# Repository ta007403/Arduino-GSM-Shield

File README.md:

Smart Coin Machine PCB (v2.1)

This project is a custom PCB for smart coin and bill acceptor machines, designed to simplify wiring, assembly, and integration with GSM modules, Arduino, and Raspberry Pi.

✨ Features

Plug & Play Wiring

Just connect +12V DC input via screw terminals.

Direct connections for coin acceptor, bill acceptor, buzzer, and status LEDs.

GSM Module Support

Compatible with SIM800L and SIM800C.

On-board relay to enable/disable GSM module.

Reset GSM via dedicated relay (Arduino Pin 7).

Built-in DC-DC step-down regulator (LM2596S) provides stable +4V supply for GSM.

Relays & Control

Coin Enable Relay → controlled by Raspberry Pi (Pin 17).

GSM Enable Relay → power cycle or disable GSM when needed.

Power Loss Relay → detect and respond to AC mains failures.

Indicators & Status LEDs

Arduino Pin 8 → Blue LED status output.

Raspberry Pi Pin 27 → Green LED status output.

GSM status LED indicators (Orange).

220VAC Detection

Input and output connectors for 220VAC detection sensor.

Useful for monitoring AC mains availability.

----------------------------------------------------------------------------------------

📐 Hardware Overview

Main components visible on the PCB:

LM2596S DC-DC Buck Converter (12V → 4V for GSM).

3 Relays:

Coin Enable Relay

GSM Enable/Reset Relay

Power Loss Relay

Connectors:

12V DC input

Coin acceptor

Bill acceptor

Buzzer

LEDs (Arduino, Raspberry Pi, GSM)

220VAC detection input/output

GSM Module Slot (SIM800L/SIM800C footprint).

(See PCB layout in uno-r4-shield-template__Assembly.pdf
 for detailed pinouts)
.

----------------------------------------------------------------------------------------

🔌 Pin Mapping
Function	Controller	Pin
Coin Enable	Raspberry Pi	GPIO17
LED Status (Green)	Raspberry Pi	GPIO27
LED Status (Blue)	Arduino	Pin 8
GSM Reset	Arduino	Pin 7
⚡ Power

Input: +12V DC

Internal Regulator: LM2596S → +4V for GSM

Relays and acceptors powered directly from +12V line.

----------------------------------------------------------------------------------------

🚀 Use Case

This PCB is ideal for:

Smart vending or refill machines.

Coin/bill based Bitcoin Lightning machines.

GSM-enabled kiosks requiring reliable reset and status handling.

----------------------------------------------------------------------------------------

📂 Repository Contents

Smart Coin PCB Version 2.1.JPG → Rendered 3D PCB view.

uno-r4-shield-template__Assembly.pdf → PCB layout & assembly reference.

README.md → This documentation.

----------------------------------------------------------------------------------------

🛠️ Assembly Notes

Connect +12V DC power input.

Wire coin and bill acceptors into screw terminals.

Install GSM module (SIM800L or SIM800C).

Connect buzzer and LED indicators.

Connect Raspberry Pi/Arduino control lines as per pin mapping.

----------------------------------------------------------------------------------------

📜 License

This project is free to use as hobby project or commercial

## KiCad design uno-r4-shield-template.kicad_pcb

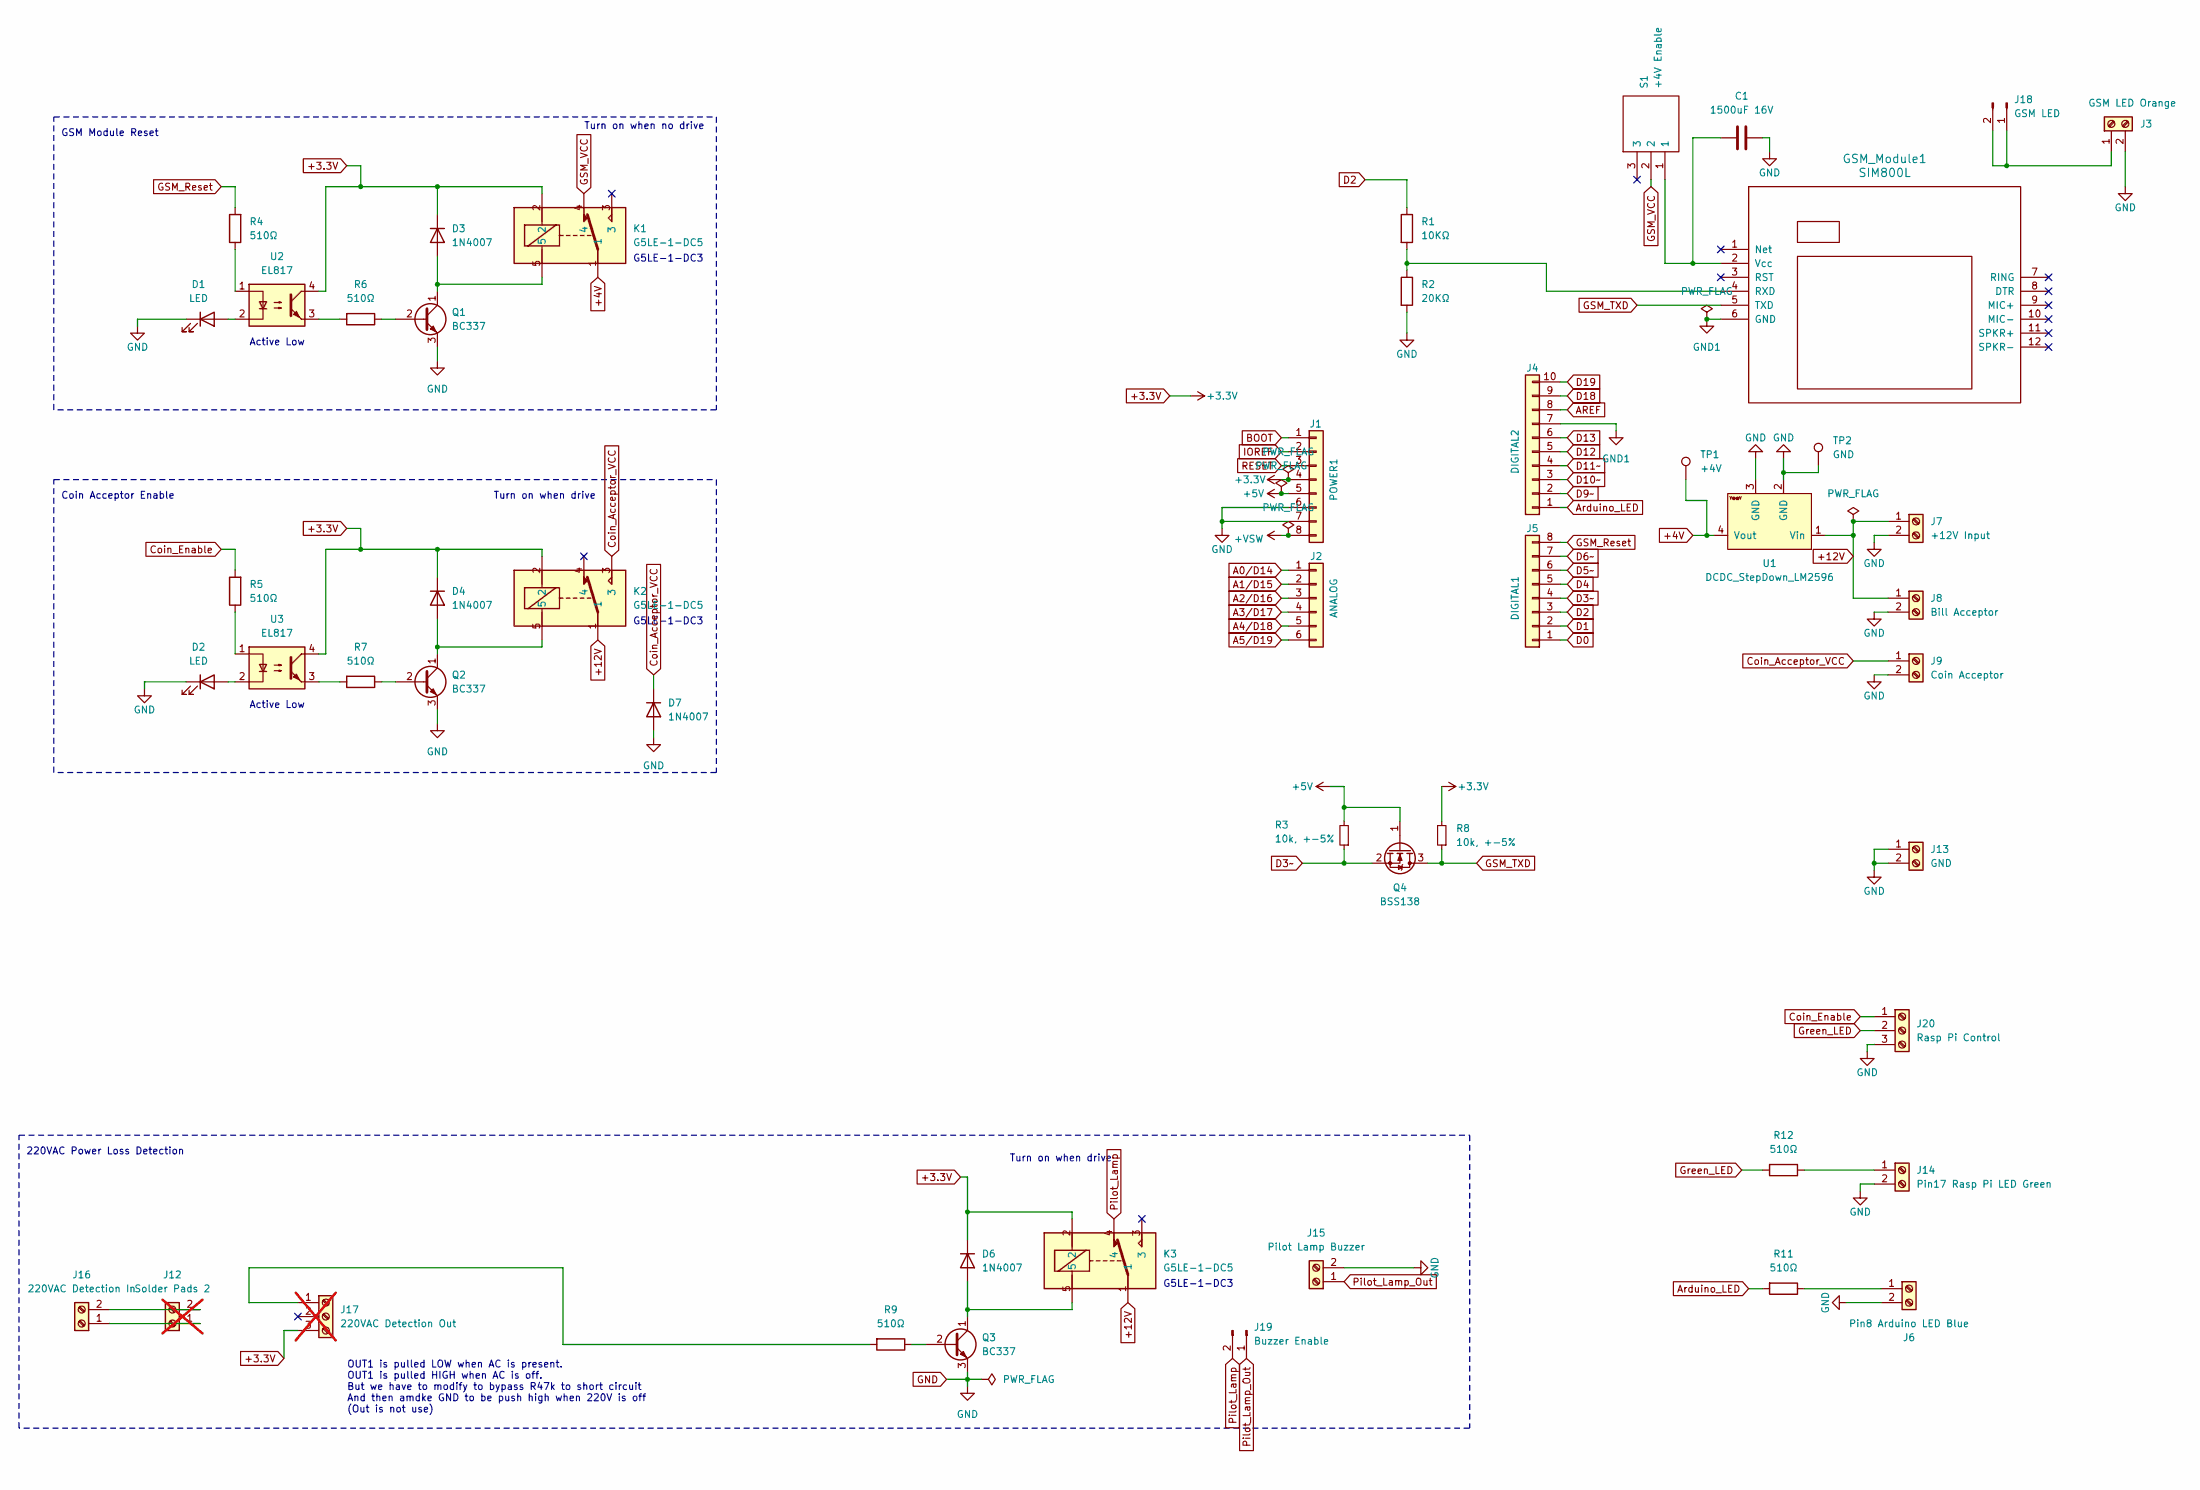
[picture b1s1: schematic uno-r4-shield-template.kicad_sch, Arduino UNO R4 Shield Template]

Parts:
C1: 1500uF 16V; CP_Radial_D10.0mm_P5.00mm
D1, D2: LED; LED_D3.0mm
D3, D4, D6, D7: 1N4007; D_DO-41_SOD81_P10.16mm_Horizontal
GSM_Module1: SIM800L
J1: POWER1; PinHeader_1x08_P2.54mm_Vertical
J2: ANALOG; PinHeader_1x06_P2.54mm_Vertical
J3: GSM LED Orange; TerminalBlock_Phoenix_MKDS-1,5-2-5.08_1x02_P5.08mm_Horizont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
J4: DIGITAL2; PinHeader_1x10_P2.54mm_Vertical
J5: DIGITAL1; PinHeader_1x08_P2.54mm_Vertical
J6: Pin8 Arduino LED Blue; TerminalBlock_Phoenix_MKDS-1,5-2-5.08_1x02_P5.08mm_Horizont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
J7: +12V Input; TerminalBlock_Phoenix_MKDS-1,5-2-5.08_1x02_P5.08mm_Horizont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
J8: Bill Acceptor; TerminalBlock_Phoenix_MKDS-1,5-2-5.08_1x02_P5.08mm_Horizont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
J9: Coin Acceptor; TerminalBlock_Phoenix_MKDS-1,5-2-5.08_1x02_P5.08mm_Horizont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
J12: Solder Pads 2; TerminalBlock_Phoenix_MKDS-1,5-2-5.08_1x02_P5.08mm_Horizont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; not fitted
J13: GND; TerminalBlock_Phoenix_MKDS-1,5-2-5.08_1x02_P5.08mm_Horizont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
J14: Pin17 Rasp Pi LED Green; TerminalBlock_Phoenix_MKDS-1,5-2-5.08_1x02_P5.08mm_Horizont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
J15: Pilot Lamp Buzzer; TerminalBlock_Phoenix_MKDS-1,5-2-5.08_1x02_P5.08mm_Horizont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
J16: 220VAC Detection In; TerminalBlock_Phoenix_MKDS-1,5-2-5.08_1x02_P5.08mm_Horizont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
J17: 220VAC Detection Out; TerminalBlock_Phoenix_MKDS-1,5-3-5.08_1x03_P5.08mm_Horizont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; not fitted
J18: GSM LED; PinHeader_1x02_P2.54mm_Vertical
J19: Buzzer Enable; PinHeader_1x02_P2.54mm_Vertical
J20: Rasp Pi Control; TerminalBlock_Phoenix_MKDS-1,5-3-5.08_1x03_P5.08mm_Horizont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
K1, K2, K3: G5LE-1-DC5; G5LE-1; Mouser Part Number 653-G5LE-1-DC5
Q1, Q2, Q3: BC337; TO-92_Inline
Q4: BSS138; SOT-23; Mfr. Part # BSS138
R1: 10KΩ; R_Axial_DIN0207_L6.3mm_D2.5mm_P10.16mm_Horizontal
R2: 20KΩ; R_Axial_DIN0207_L6.3mm_D2.5mm_P10.16mm_Horizontal
R3, R8: 10k, +-5%; R_Axial_DIN0204_L3.6mm_D1.6mm_P5.08mm_Horizontal; Mfr. Part # RT0402FRE0710KL; LCSC Part # C25804
R4, R5, R6, R7, R9, R11, R12: 510Ω; R_Axial_DIN0207_L6.3mm_D2.5mm_P10.16mm_Horizontal
S1: +4V Enable; 2MS1T1B3M2QES; Mouser Part Number 118-2MS1T1B3M2QES
TP1: +4V; TestPoint_Pad_1.0x1.0mm
TP2: GND; TestPoint_Pad_1.0x1.0mm
U1: DCDC_StepDown_LM2596; YAAJ_DCDC_StepDown_LM2596
U2, U3: EL817; DIP-4_W7.62mm

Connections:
+3.3V: D3.1 (K), D4.1 (K), D6.1 (K), J1.4, J17.3, K1.2, K2.2, K3.2, R8.2, U2.4, U3.4
+4V: K1.1, TP1.1, U1.4 (Vout)
+5V: J1.5, Q4.1 (G), R3.2
+12V: J7.1, J8.1, K2.1, K3.1, U1.1 (Vin)
+VSW: J1.8
A0/D14: J2.1
A1/D15: J2.2
A2/D16: J2.3
A3/D17: J2.4
A4/D18: J2.5
A5/D19: J2.6
AREF: J4.8
Arduino_LED: J4.1, R11.2
BOOT: J1.1
Coin_Acceptor_VCC: D7.1 (K), J9.1, K2.3
Coin_Enable: J20.1, R5.2
D0: J5.1
D1: J5.2
D2: J5.3, R1.1
D3~: J5.4, Q4.2 (S), R3.1
D4: J5.5
D5~: J5.6
D6~: J5.7
D9~: J4.2
D10~: J4.3
D11~: J4.4
D12: J4.5
D13: J4.6
D18: J4.9
D19: J4.10
GND: C1.2, D1.1 (K), D2.1 (K), D7.2 (A), J1.6, J1.7, J3.2, J6.2, J7.2, J8.2, J9.2, J13.1, J13.2, J14.2, J15.2, J20.3, Q1.3 (E), Q2.3 (E), Q3.3 (E), R2.2, TP2.1, U1.2 (GND), U1.3 (GND)
GND1: GSM_Module1.6 (GND), J4.7
GSM_Reset: J5.8, R4.2
GSM_TXD: GSM_Module1.5 (TXD), Q4.3 (D), R8.1
GSM_VCC: K1.4, S1.2
Green_LED: J20.2, R12.2
IOREF: J1.2
unnamed: D1.2 (A), U2.2
unnamed: D2.2 (A), U3.2
unnamed: D3.2 (A), K1.5, Q1.1 (C)
unnamed: D4.2 (A), K2.5, Q2.1 (C)
unnamed: D6.2 (A), K3.5, Q3.1 (C)
unnamed: GSM_Module1.4 (RXD), R1.2, R2.1
unnamed: C1.1, GSM_Module1.2 (Vcc), S1.1
unnamed: J6.1, R11.1
unnamed: J12.1, J16.1
unnamed: J12.2, J16.2
unnamed: J14.1, R12.1
unnamed: J17.1, R9.2
unnamed: J3.1, J18.1, J18.2
unnamed: Q1.2 (B), R6.1
unnamed: Q2.2 (B), R7.1
unnamed: Q3.2 (B), R9.1
unnamed: R4.1, U2.1
unnamed: R5.1, U3.1
unnamed: R6.2, U2.3
unnamed: R7.2, U3.3
Pilot_Lamp: J19.2, K3.4
Pilot_Lamp_Out: J15.1, J19.1
RESET: J1.3

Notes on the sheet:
G5LE-1-DC3
Active Low
Turn on when drive
Coin Acceptor Enable
GSM Module Reset
Turn on when no drive
OUT1 is pulled LOW when AC is present. OUT1 is pulled HIGH when AC is off. But we have to modify to bypass R47k to short circuit And then amdke GND to be push high when 220V is off (Out is not use)
220VAC Power Loss Detection

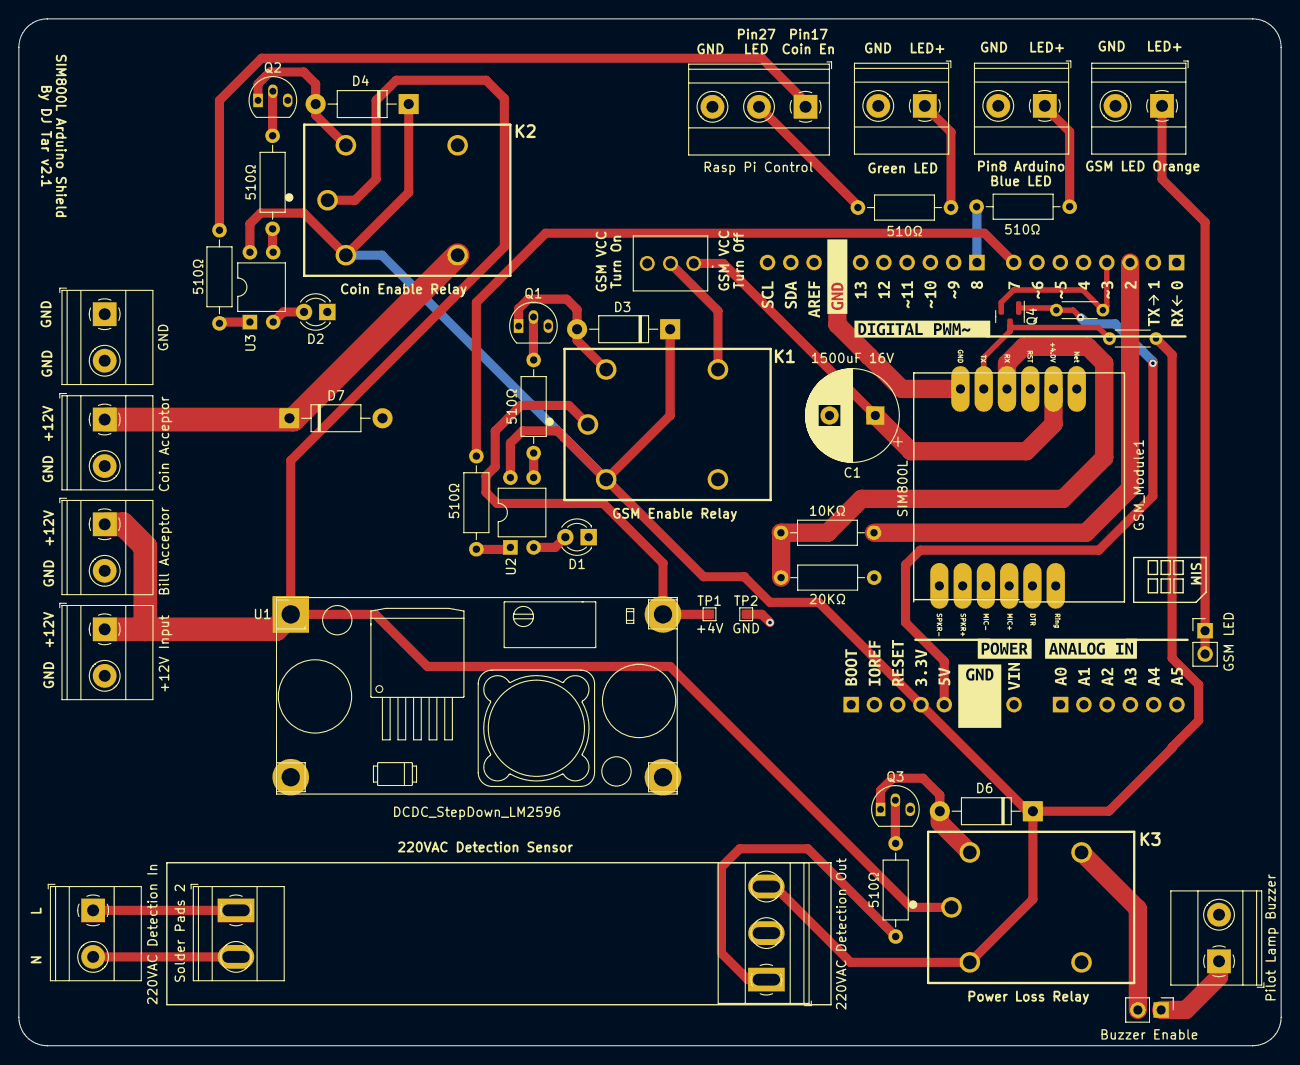
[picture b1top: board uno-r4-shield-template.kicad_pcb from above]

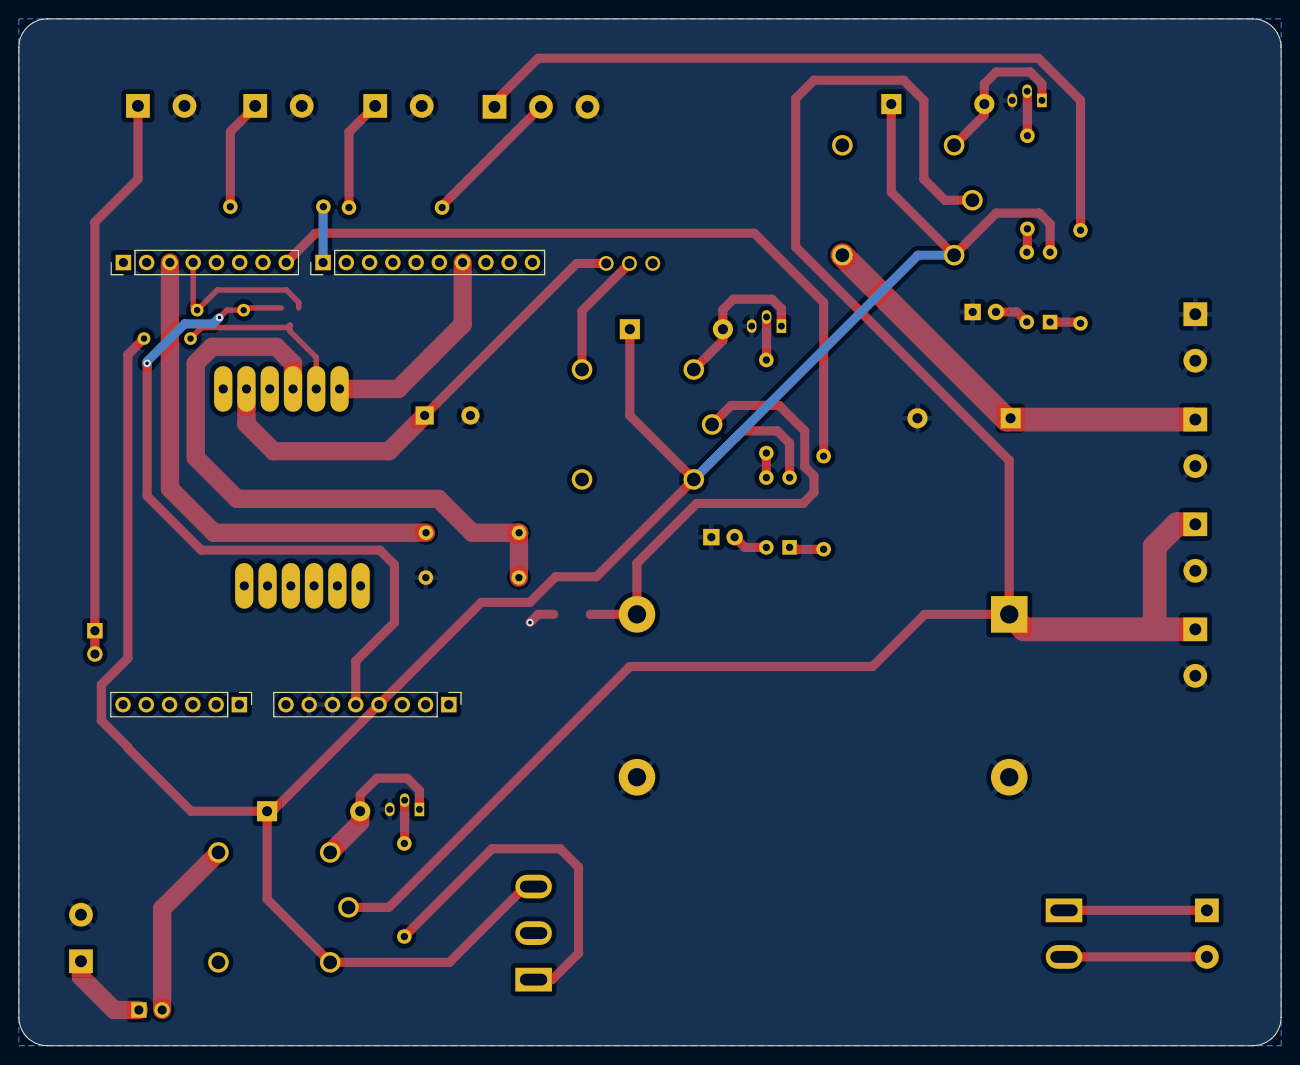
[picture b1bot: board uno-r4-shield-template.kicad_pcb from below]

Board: 2 copper layers, 137.8 x 112.1 mm, 86 parts (4 on the bottom side), 37 nets.

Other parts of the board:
kibuzzard-64EA1AE1: G***; kibuzzard-64EA1AE1
kibuzzard-64EA1B1D: G***; kibuzzard-64EA1B1D
kibuzzard-64EA1B42: G***; kibuzzard-64EA1B42
kibuzzard-64EA15CB: G***; kibuzzard-64EA15CB
kibuzzard-64EA16B9: G***; kibuzzard-64EA16B9
kibuzzard-64EA153F: G***; kibuzzard-64EA153F
kibuzzard-64EA162C: G***; kibuzzard-64EA162C
kibuzzard-64EA177C: G***; kibuzzard-64EA177C
kibuzzard-64EA1511: G***; kibuzzard-64EA1511
kibuzzard-64EA1739: G***; kibuzzard-64EA1739
kibuzzard-64EA1767: G***; kibuzzard-64EA1767
kibuzzard-636462BB: G***; kibuzzard-636462BB
kibuzzard-636463B1: G***; kibuzzard-636463B1
kibuzzard-636463C7: G***; kibuzzard-636463C7
kibuzzard-636463E3: G***; kibuzzard-636463E3
kibuzzard-636464C1: G***; kibuzzard-636464C1
kibuzzard-636464E7: G***; kibuzzard-636464E7
kibuzzard-636465A9: G***; kibuzzard-636465A9
kibuzzard-636466AF: G***; kibuzzard-636466AF
kibuzzard-6364607A: G***; kibuzzard-6364607A
kibuzzard-6364651D: G***; kibuzzard-6364651D
kibuzzard-6364657A: G***; kibuzzard-6364657A
kibuzzard-6364668F: G***; kibuzzard-6364668F
kibuzzard-6364669B: G***; kibuzzard-6364669B
kibuzzard-63646068: G***; kibuzzard-63646068
kibuzzard-63646358: G***; kibuzzard-63646358
kibuzzard-63646507: G***; kibuzzard-63646507
kibuzzard-63646512: G***; kibuzzard-63646512
kibuzzard-63646593: G***; kibuzzard-63646593
kibuzzard-63646605: G***; kibuzzard-63646605
kibuzzard-63646671: G***; kibuzzard-63646671
kibuzzard-63646688: G***; kibuzzard-63646688
kibuzzard-63646694: G***; kibuzzard-63646694
kibuzzard-63656678: G***; kibuzzard-63656678
kibuzzard-63659483: G***; kibuzzard-63659483
kibuzzard-63659489: G***; kibuzzard-63659489
